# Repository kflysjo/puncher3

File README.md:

# puncher3
open source punch-tracker

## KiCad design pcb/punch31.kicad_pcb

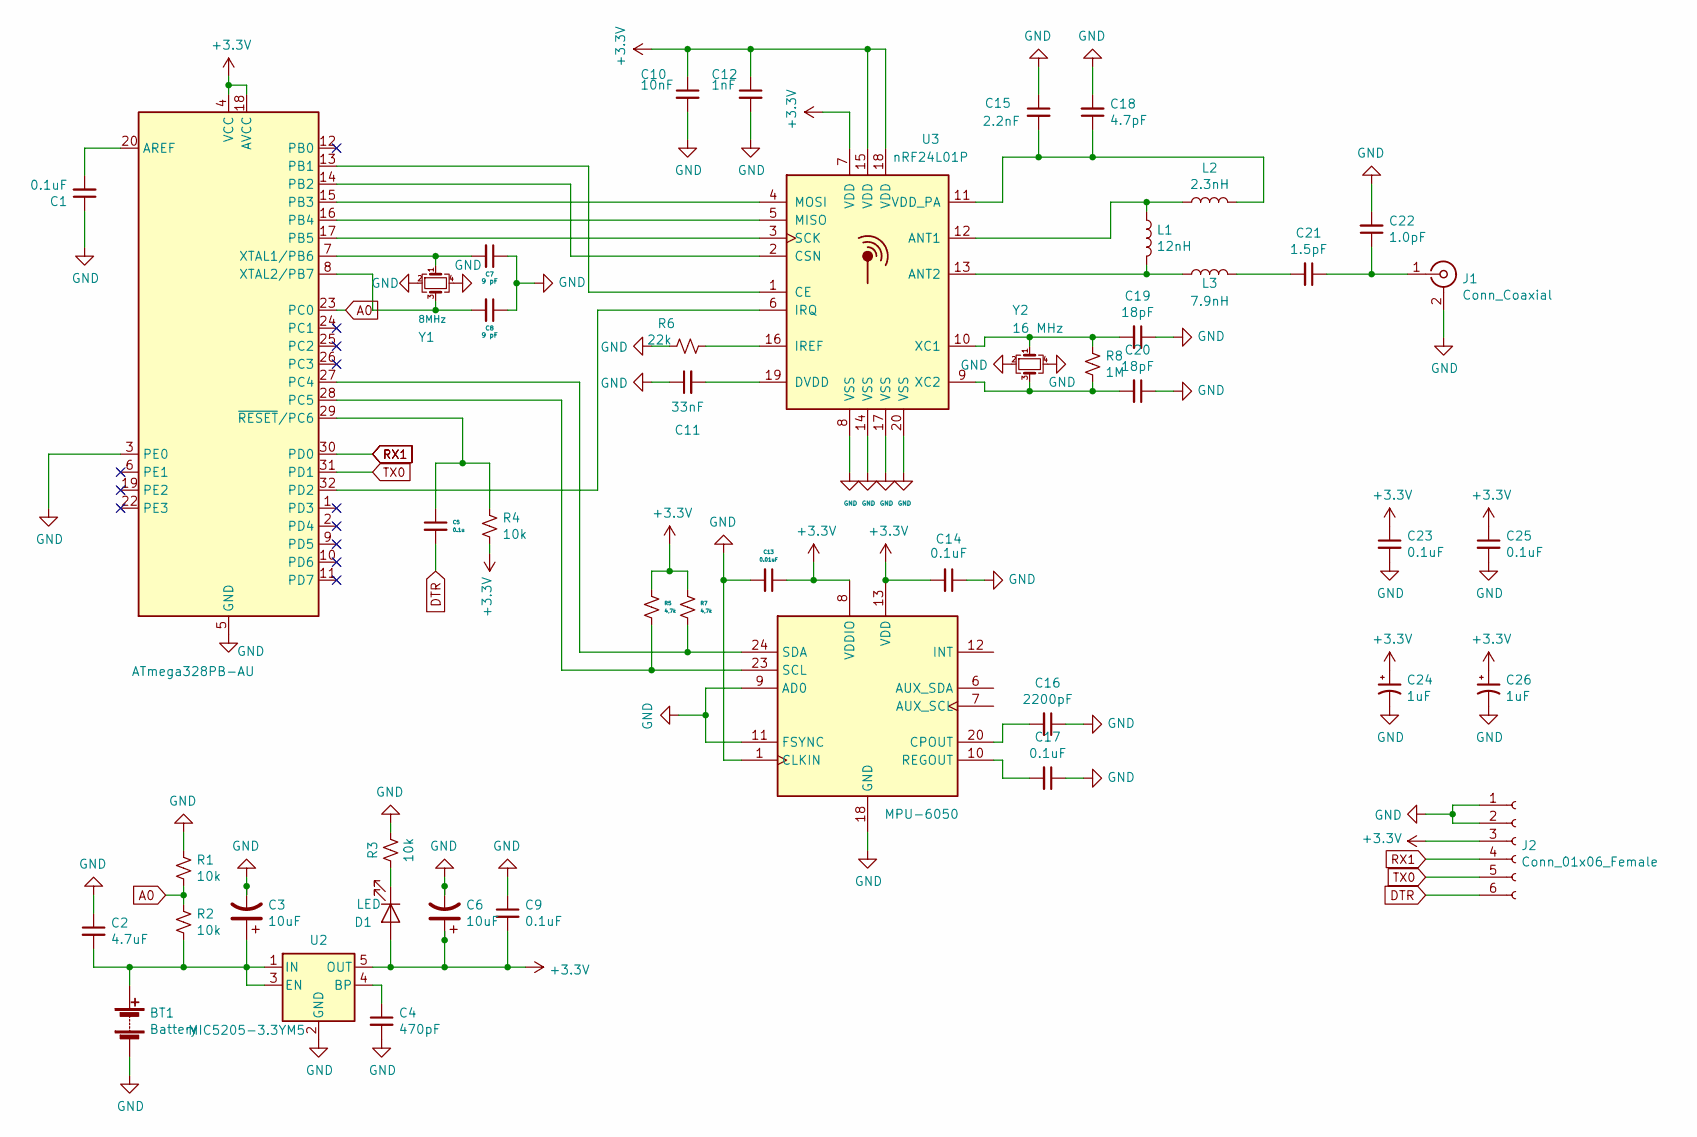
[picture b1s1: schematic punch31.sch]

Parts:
BT1: Battery; JST_EH_S2B-EH_1x02_P2.50mm_Horizontal
C1, C9, C14, C17, C23, C25: 0.1uF; C_0402_1005Metric
C2: 4.7uF; C_0402_1005Metric
C3, C6: 10uF; C_0402_1005Metric
C4: 470pF; C_0402_1005Metric
C5: 0.1u; C_0402_1005Metric
C7, C8: 9 pF; C_0402_1005Metric
C10: 10nF; C_0402_1005Metric
C11: 33nF; C_0402_1005Metric
C12: 1nF; C_0402_1005Metric
C13: 0.01uF; C_0402_1005Metric
C15: 2.2nF; C_0402_1005Metric
C16: 2200pF; C_0402_1005Metric
C18: 4.7pF; C_0402_1005Metric
C19, C20: 18pF; C_0402_1005Metric
C21: 1.5pF; C_0402_1005Metric
C22: 1.0pF; C_0402_1005Metric
C24, C26: 1uF; CP_Elec_4x4.5
D1: LED; D_0402_1005Metric
J1: Conn_Coaxial; 2500_MHz_Theta3
J2: Conn_01x06_Female; PinHeader_1x06_P2.54mm_Vertical
L1: 12nH; L_0402_1005Metric
L2: 2.3nH; L_0402_1005Metric
L3: 7.9nH; L_0402_1005Metric
R1, R2, R3, R4: 10k; R_0402_1005Metric
R5, R7: 4,7k; R_0402_1005Metric
R6: 22k; R_0402_1005Metric
R8: 1M; R_0402_1005Metric
U1: ATmega328PB-AU; TQFP-32_7x7mm_P0.8mm
U2: MIC5205-3.3YM5; SOT-23-5
U3: nRF24L01P; QFN-20-1EP_4x4mm_P0.5mm_EP2.5x2.5mm
U4: MPU-6050; InvenSense_QFN-24_4x4mm_P0.5mm
Y1: 8MHz; ECS-80-18-33-JGN-TR
Y2: 16 MHz; ECS1637

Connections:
+3V3: C6.1, C9.2, C10.1, C12.1, C13.1, C14.2, C23.1, C24.1, C25.1, C26.1, D1.2 (A), J2.3, R4.2, R5.1, R7.1, U1.4 (VCC), U1.18 (AVCC), U2.5 (OUT), U3.7 (VDD), U3.15 (VDD), U3.18 (VDD), U4.8 (VDDIO), U4.13 (VDD)
A0: R1.2, R2.1, U1.23 (PC0)
DTR: C5.2, J2.6
GND: BT1.2 (-), C1.1, C2.1, C3.2, C4.2, C6.2, C7.1, C8.1, C9.1, C10.2, C11.1, C12.2, C13.2, C14.1, C15.1, C16.1, C17.1, C18.2, C19.1, C20.1, C22.2, C23.2, C24.2, C25.2, C26.2, J1.2 (Ext), J2.1, J2.2, R1.1, R3.2, R6.2, U1.3 (PE0), U1.5 (GND), U1.21 (GND), U2.2 (GND), U3.8 (VSS), U3.14 (VSS), U3.17 (VSS), U3.20 (VSS), U4.1 (CLKIN), U4.9 (AD0), U4.11 (FSYNC), U4.18 (GND), Y1.2, Y1.4, Y2.2, Y2.4
unnamed: BT1.1 (+), C2.2, C3.1, R2.2, U2.1 (IN), U2.3 (EN)
unnamed: C1.2, U1.20 (AREF)
unnamed: C4.1, U2.4 (BP)
unnamed: C5.1, R4.1, U1.29 (~RESET~/PC6)
unnamed: C7.2, U1.7 (XTAL1/PB6), Y1.1
unnamed: C8.2, U1.8 (XTAL2/PB7), Y1.3
unnamed: C11.2, U3.19 (DVDD)
unnamed: C15.2, C18.1, L2.2, U3.11 (VDD_PA)
unnamed: C16.2, U4.20 (CPOUT)
unnamed: C17.2, U4.10 (REGOUT)
unnamed: C19.2, R8.1, U3.10 (XC1), Y2.1
unnamed: C20.2, R8.2, U3.9 (XC2), Y2.3
unnamed: C21.1, C22.1, J1.1 (In)
unnamed: C21.2, L3.2
unnamed: D1.1 (K), R3.1
unnamed: L1.1, L2.1, U3.12 (ANT1)
unnamed: L1.2, L3.1, U3.13 (ANT2)
unnamed: R5.2, U1.28 (PC5), U4.23 (SCL)
unnamed: R6.1, U3.16 (IREF)
unnamed: R7.2, U1.27 (PC4), U4.24 (SDA)
unnamed: U1.13 (PB1), U3.1 (CE)
unnamed: U1.14 (PB2), U3.2 (CSN)
unnamed: U1.15 (PB3), U3.4 (MOSI)
unnamed: U1.16 (PB4), U3.5 (MISO)
unnamed: U1.17 (PB5), U3.3 (SCK)
unnamed: U1.32 (PD2), U3.6 (IRQ)
RX1: J2.4, U1.30 (PD0)
TX0: J2.5, U1.31 (PD1)

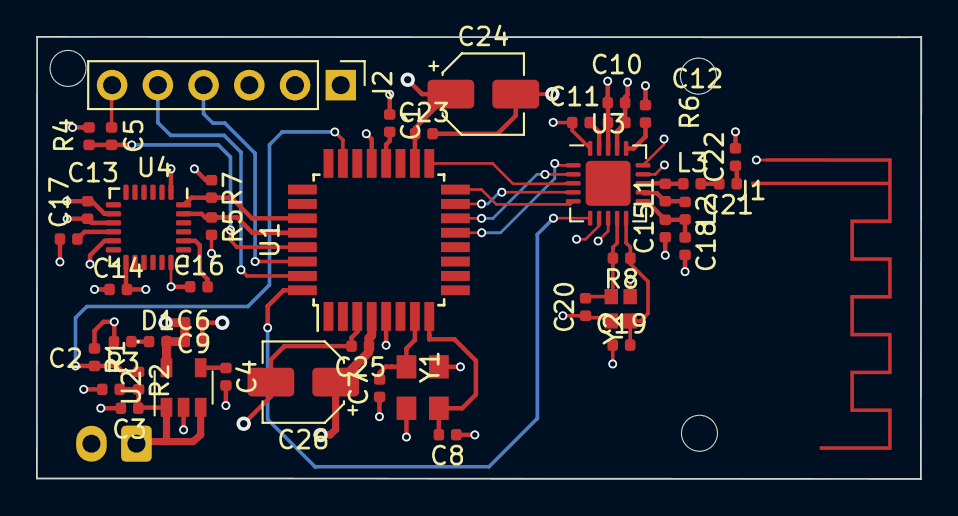
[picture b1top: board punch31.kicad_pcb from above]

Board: 4 copper layers, 49.1 x 24.6 mm, 47 parts (1 on the bottom side), 32 nets.
